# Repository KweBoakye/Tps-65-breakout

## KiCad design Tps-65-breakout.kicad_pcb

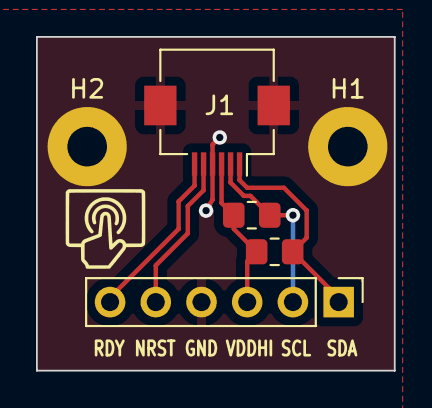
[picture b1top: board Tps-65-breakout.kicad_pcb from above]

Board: 2 copper layers, 19.9 x 18.5 mm, 6 parts (0 on the bottom side), 6 nets.

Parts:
H1, H2: MountingHole; MountingHole_2.2mm_M2_Pad
J1: Conn_01x06_Pin; Hirose_FH12-6S-0.5SH_1x06-1MP_P0.50mm_Horizontal
J2: Conn_01x06_Socket; PinHeader_1x06_P2.54mm_Vertical
R1, R2: 4k7; R_0805_2012Metric_Pad1.20x1.40mm_HandSolder

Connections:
GND: H1.1, H2.1, J1.4, J1.MP, J2.4
NRST: J1.5, J2.5
RDY: J1.6, J2.6
SCL: J1.2, J2.2, R1.1
SDA: J1.1, J2.1, R2.1
VDDHI: J1.3, J2.3, R1.2, R2.2

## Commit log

2023-08-12 Initial commit of completed board
2023-08-12 deleted outdated production files
2023-08-23 improved routing and grounded mounting holes
2023-08-29 reversed pin order, grounded ffc connector, added silkscreens
2023-08-30 corrected pin silkscreen labels
